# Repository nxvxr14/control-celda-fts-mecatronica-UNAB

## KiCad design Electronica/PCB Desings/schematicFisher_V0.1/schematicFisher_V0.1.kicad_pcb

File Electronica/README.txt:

*3D: Archivos .STL de componentes electrónicos no incluidos en las librerías de KiCad.
*Datasheets: Documentos en formato .pdf de las especificaciones de los distintos componentes utilizados en las tarjetas.
*Esquemáticos de referencia: Documentos .pdf con los esquemáticos de algunas tarjetas Arduino.
*Esquemáticos finales PDF: Documentos .pdf con los esquemáticos definitivos de las tarjetas del proyecto.
*Huellas y símbolos: Archivos de componentes necesarios que no se encuentran en las librerías nativas de KiCad.
*Imágenes: Archivos .PNG con las vistas 3D de las tarjetas.
*PCB Designs: Incluye los cuatro diseños electrónicos, con sus respectivos esquemáticos, símbolos, ruteados y referencias de componentes para su fabricación en JLCPCB, se abre con Kicad 7.0 o más:

-schematicFisher: Tarjeta para la adecuación de señales, convirtiendo voltajes de 9V a 24V y viceversa.
-schematicPLC: Tarjeta principal del PLC.
-schematicPowerSourcePLC: Tarjeta de alimentación para el PLC, con las fuentes de voltaje necesarias.
-schematicShieldPLC: Tarjeta diseñada para conectar un Arduino Mega al PLC.

*plcIMG.pretty: Archivo generado automáticamente por KiCad.
*Recortes de placa: No utilizado en el proyecto.
*Simulaciones: Simulaciones de los distintos circuitos implementados, realizadas en Proteus.

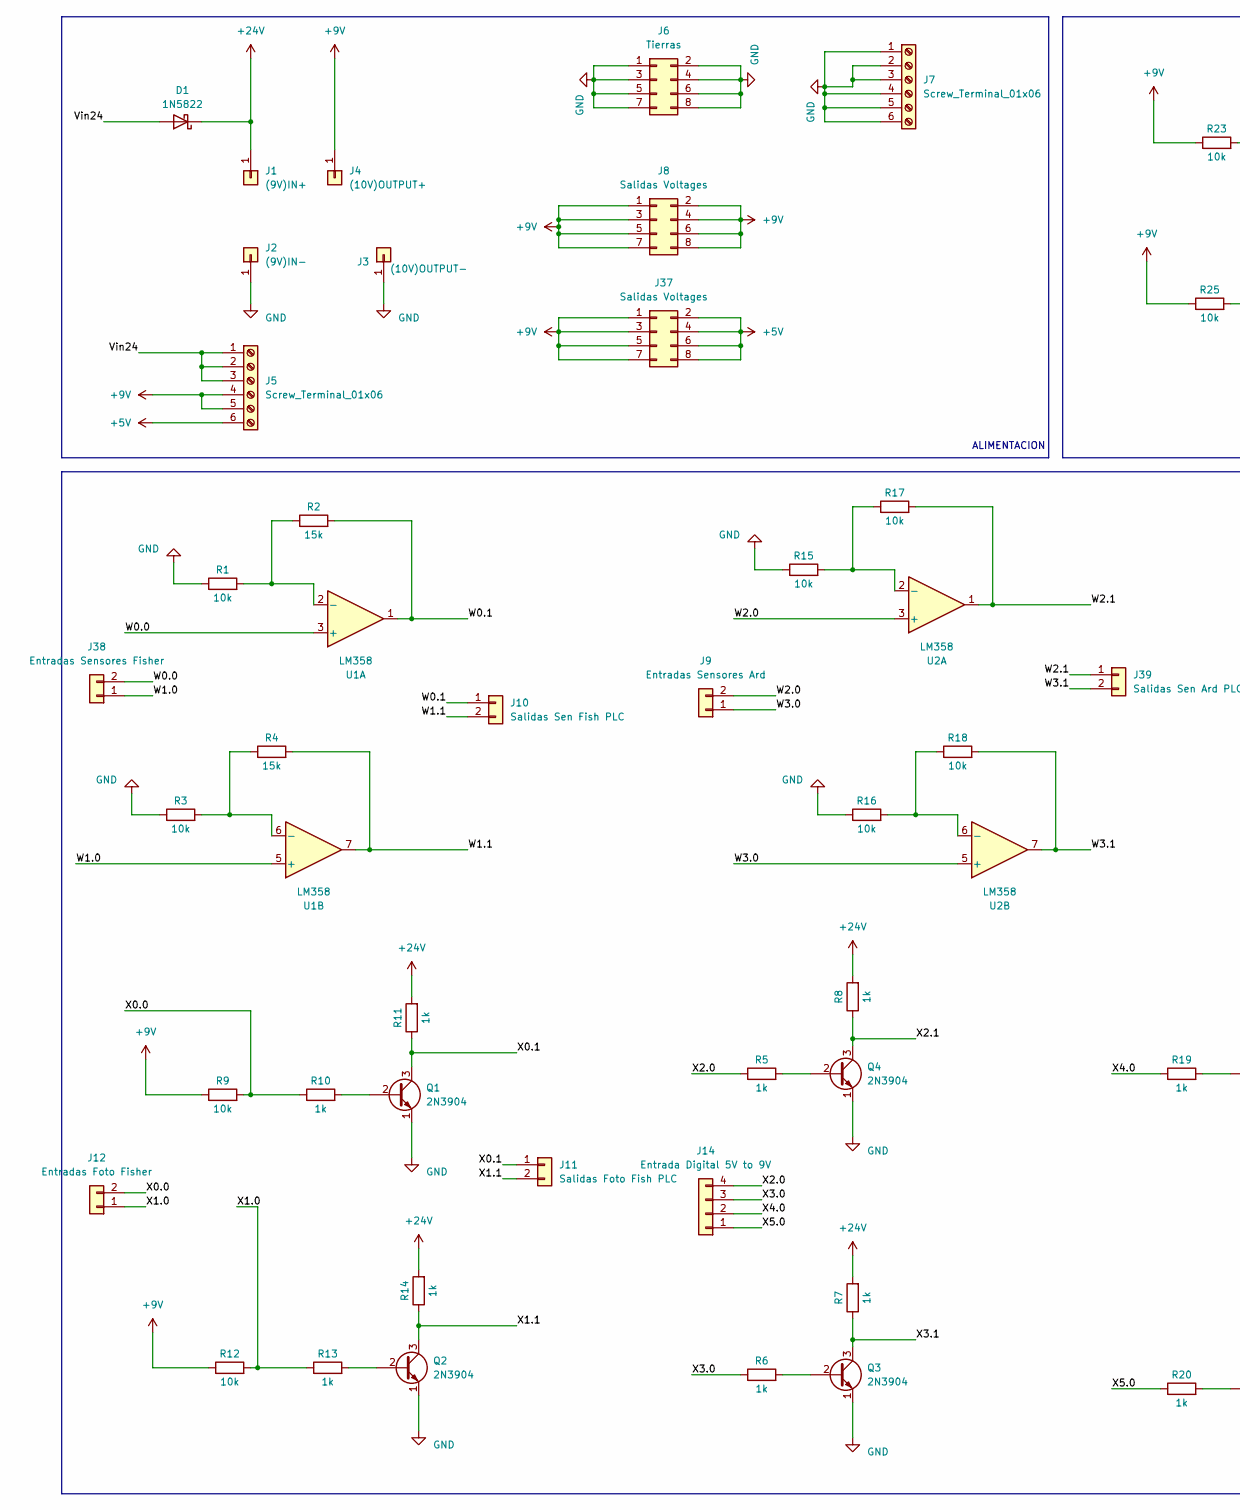
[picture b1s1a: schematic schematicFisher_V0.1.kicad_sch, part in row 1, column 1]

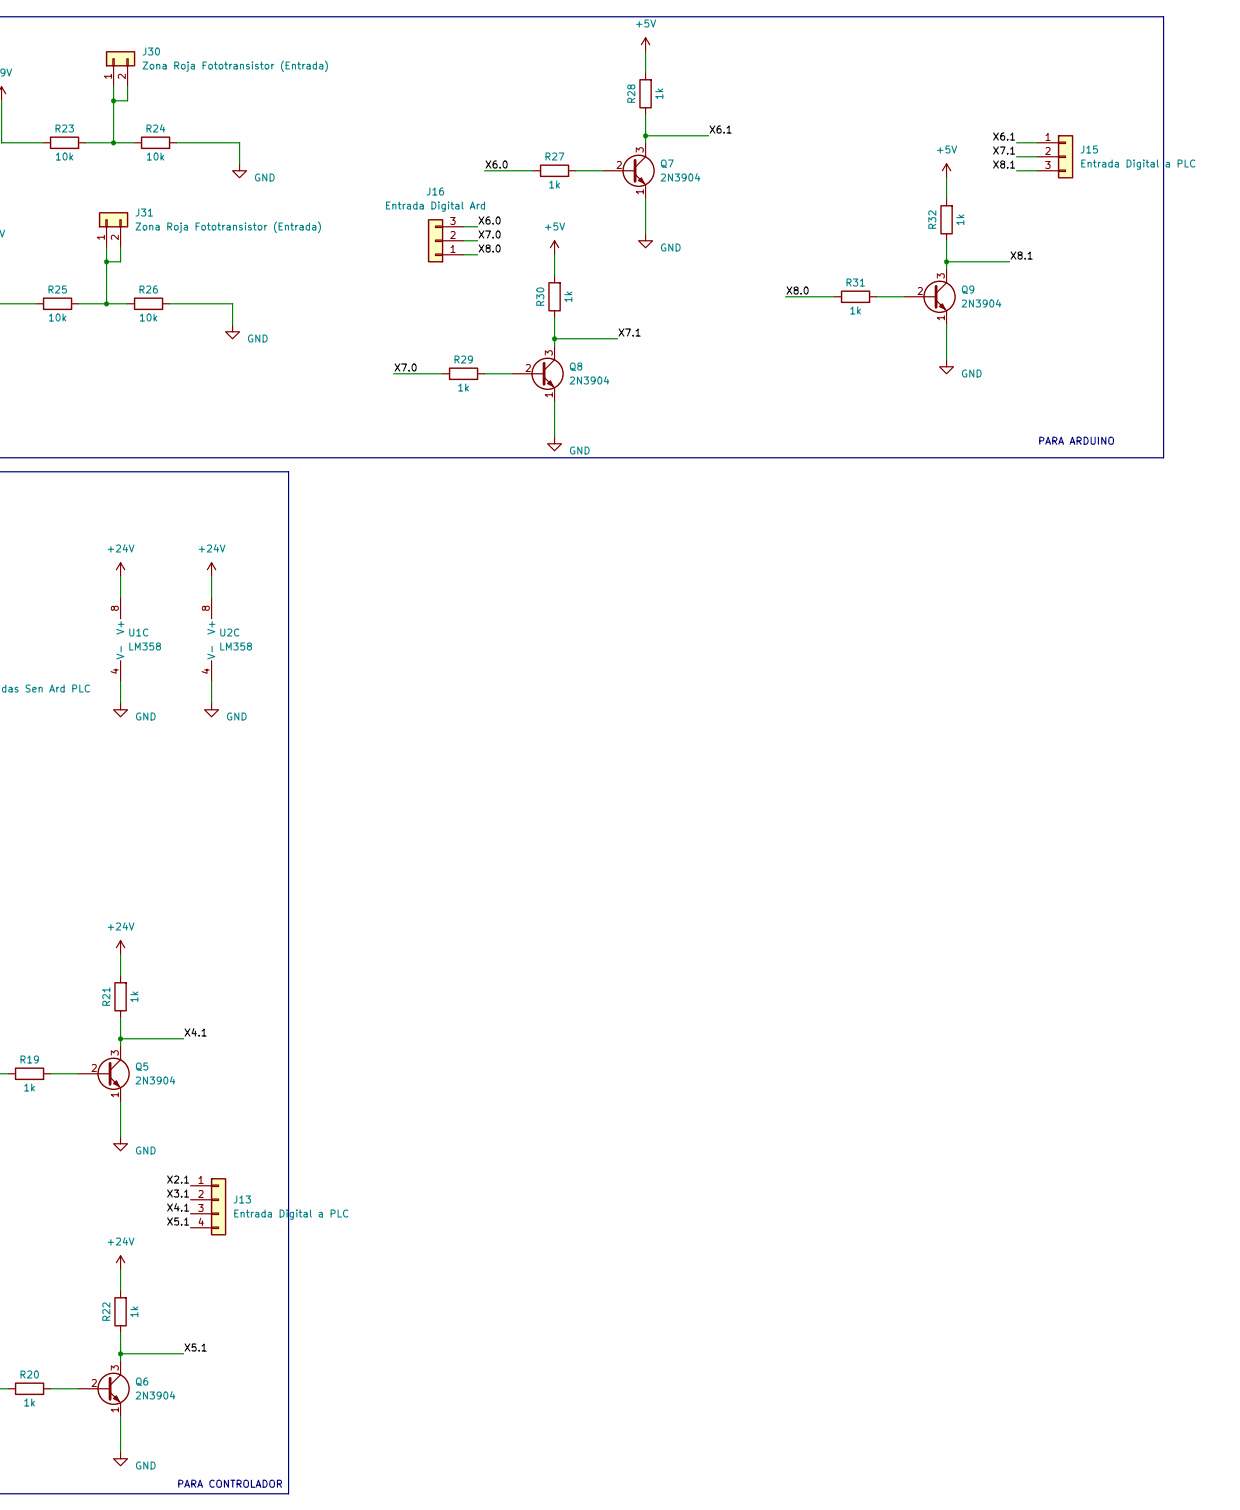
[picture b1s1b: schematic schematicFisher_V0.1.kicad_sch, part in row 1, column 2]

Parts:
D1: 1N5822; D_DO-201AD_P15.24mm_Horizontal
J1: (9V)IN+; PinSocket_1x01_P2.54mm_Vertical
J2: (9V)IN-; PinSocket_1x01_P2.54mm_Vertical
J3: (10V)OUTPUT-; PinSocket_1x01_P2.54mm_Vertical
J4: (10V)OUTPUT+; PinSocket_1x01_P2.54mm_Vertical
J5, J7: Screw_Terminal_01x06; TerminalBlock_Phoenix_MKDS-1,5-6_1x06_P5.00mm_Horizontal
J6: Tierras; PinHeader_2x04_P2.54mm_Vertical
J8, J37: Salidas Voltages; PinSocket_2x04_P2.54mm_Vertical
J9: Entradas Sensores Ard; PinHeader_1x02_P2.54mm_Vertical
J10: Salidas Sen Fish PLC; PinHeader_1x02_P2.54mm_Vertical
J11: Salidas Foto Fish PLC; PinHeader_1x02_P2.54mm_Vertical
J12: Entradas Foto Fisher; PinHeader_1x02_P2.54mm_Vertical
J13: Entrada Digital a PLC; PinHeader_1x04_P2.54mm_Vertical
J14: Entrada Digital 5V to 9V; PinHeader_1x04_P2.54mm_Vertical
J15: Entrada Digital a PLC; PinHeader_1x03_P2.54mm_Vertical
J16: Entrada Digital Ard; PinHeader_1x03_P2.54mm_Vertical
J30, J31: Zona Roja Fototransistor (Entrada); PinHeader_1x02_P2.54mm_Vertical
J38: Entradas Sensores Fisher; PinHeader_1x02_P2.54mm_Vertical
J39: Salidas Sen Ard PLC; PinHeader_1x02_P2.54mm_Vertical
Q1, Q2, Q3, Q4, Q5, Q6, Q7, Q8, Q9: 2N3904; TO-92_Inline
R1, R3, R9, R12, R15, R16, R17, R18, R23, R24, R25, R26: 10k; R_Axial_DIN0204_L3.6mm_D1.6mm_P5.08mm_Horizontal
R2, R4: 15k; R_Axial_DIN0204_L3.6mm_D1.6mm_P5.08mm_Horizontal
R5, R6, R7, R8, R10, R11, R13, R14, R19, R20, R21, R22, R27, R28, R29, R30, R31, R32: 1k; R_Axial_DIN0204_L3.6mm_D1.6mm_P5.08mm_Horizontal
U1, U2: LM358; DIP-8_W7.62mm_LongPads

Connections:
+5V: J5.6, J37.2, J37.4, J37.6, J37.8, R28.2, R30.2, R32.2
+9V: J4.1, J5.4, J5.5, J8.1, J8.2, J8.3, J8.4, J8.5, J8.6, J8.7, J8.8, J37.1, J37.3, J37.5, J37.7, R9.1, R12.1, R23.1, R25.1
+24V: D1.1 (K), J1.1, R7.2, R8.2, R11.2, R14.2, R21.2, R22.2, U1.8 (V+), U2.8 (V+)
/Vin24: D1.2 (A), J5.1, J5.2, J5.3
/W0.0: J38.2, U1.3 (+)
/W0.1: J10.1, R2.2, U1.1
/W1.0: J38.1, U1.5 (+)
/W1.1: J10.2, R4.2, U1.7
/W2.0: J9.2, U2.3 (+)
/W2.1: J39.1, R17.2, U2.1
/W3.0: J9.1, U2.5 (+)
/W3.1: J39.2, R18.2, U2.7
/X0.0: J12.2, R9.2, R10.1
/X0.1: J11.1, Q1.3 (C), R11.1
/X1.0: J12.1, R12.2, R13.1
/X1.1: J11.2, Q2.3 (C), R14.1
/X2.0: J14.4, R5.1
/X2.1: J13.1, Q4.3 (C), R8.1
/X3.0: J14.3, R6.1
/X3.1: J13.2, Q3.3 (C), R7.1
/X4.0: J14.2, R19.1
/X4.1: J13.3, Q5.3 (C), R21.1
/X5.0: J14.1, R20.1
/X5.1: J13.4, Q6.3 (C), R22.1
/X6.0: J16.3, R27.1
/X6.1: J15.1, Q7.3 (C), R28.1
/X7.0: J16.2, R29.1
/X7.1: J15.2, Q8.3 (C), R30.1
/X8.0: J16.1, R31.1
/X8.1: J15.3, Q9.3 (C), R32.1
GND: J2.1, J3.1, J6.1, J6.2, J6.3, J6.4, J6.5, J6.6, J6.7, J6.8, J7.1, J7.2, J7.3, J7.4, J7.5, J7.6, Q1.1 (E), Q2.1 (E), Q3.1 (E), Q4.1 (E), Q5.1 (E), Q6.1 (E), Q7.1 (E), Q8.1 (E), Q9.1 (E), R1.1, R3.1, R15.1, R16.1, R24.2, R26.2, U1.4 (V-), U2.4 (V-)
unnamed: J30.1, J30.2, R23.2, R24.1
unnamed: J31.1, J31.2, R25.2, R26.1
unnamed: Q1.2 (B), R10.2
unnamed: Q2.2 (B), R13.2
unnamed: Q3.2 (B), R6.2
unnamed: Q4.2 (B), R5.2
unnamed: Q5.2 (B), R19.2
unnamed: Q6.2 (B), R20.2
unnamed: Q7.2 (B), R27.2
unnamed: Q8.2 (B), R29.2
unnamed: Q9.2 (B), R31.2
unnamed: R1.2, R2.1, U1.2 (-)
unnamed: R3.2, R4.1, U1.6 (-)
unnamed: R15.2, R17.1, U2.2 (-)
unnamed: R16.2, R18.1, U2.6 (-)

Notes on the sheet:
PARA CONTROLADOR
PARA ARDUINO
ALIMENTACION

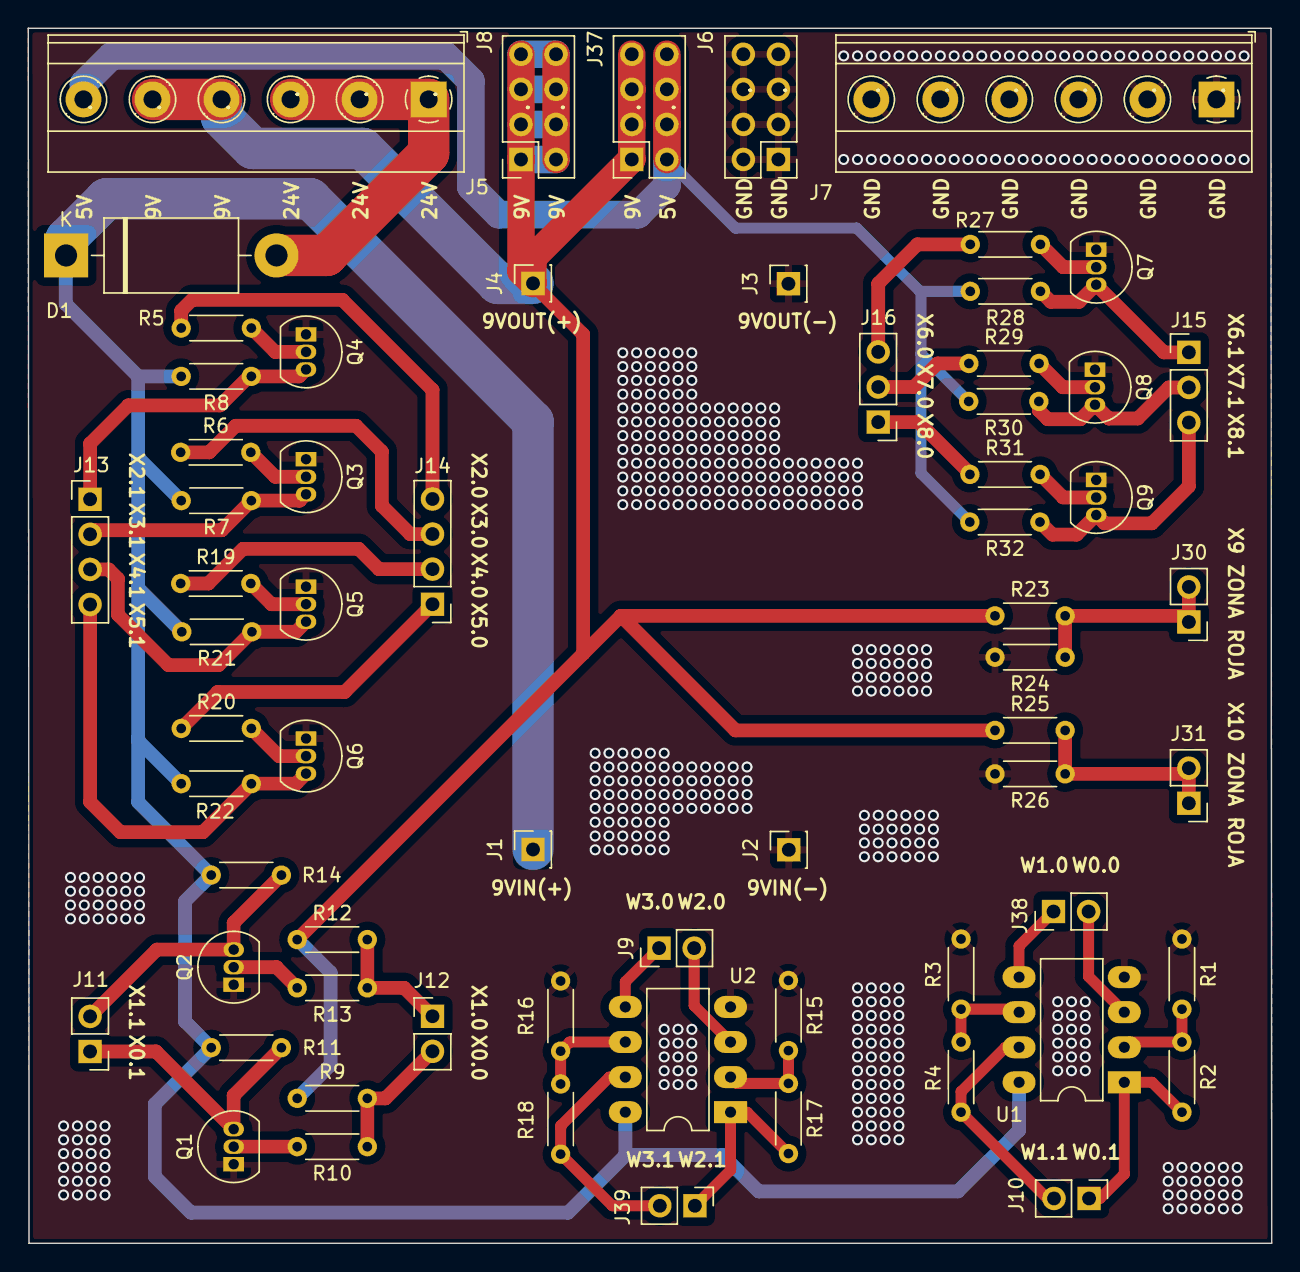
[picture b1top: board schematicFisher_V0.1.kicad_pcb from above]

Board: 2 copper layers, 90.1 x 88.0 mm, 65 parts (0 on the bottom side), 46 nets.

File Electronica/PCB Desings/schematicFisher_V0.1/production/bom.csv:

Designator,Footprint,Quantity,Value,LCSC Part #
D1,D_DO-201AD_P15.24mm_Horizontal,1,1N5822,
J1,PinSocket_1x01_P2.54mm_Vertical,1,(9V)IN+,
J10,PinHeader_1x02_P2.54mm_Vertical,1,Salidas Sen Fish PLC,
J11,PinHeader_1x02_P2.54mm_Vertical,1,Salidas Foto Fish PLC,
J12,PinHeader_1x02_P2.54mm_Vertical,1,Entradas Foto Fisher,
J13,PinHeader_1x04_P2.54mm_Vertical,1,Entrada Digital a PLC,
J14,PinHeader_1x04_P2.54mm_Vertical,1,Entrada Digital 5V to 9V,
J15,PinHeader_1x03_P2.54mm_Vertical,1,Entrada Digital a PLC,
J16,PinHeader_1x03_P2.54mm_Vertical,1,Entrada Digital Ard,
J2,PinSocket_1x01_P2.54mm_Vertical,1,(9V)IN-,
J3,PinSocket_1x01_P2.54mm_Vertical,1,(10V)OUTPUT-,
"J30, J31",PinHeader_1x02_P2.54mm_Vertical,2,Zona Roja Fototransistor (Entrada),
"J37, J8",PinSocket_2x04_P2.54mm_Vertical,2,Salidas Voltages,
J38,PinHeader_1x02_P2.54mm_Vertical,1,Entradas Sensores Fisher,
J39,PinHeader_1x02_P2.54mm_Vertical,1,Salidas Sen Ard PLC,
J4,PinSocket_1x01_P2.54mm_Vertical,1,(10V)OUTPUT+,
"J5, J7","TerminalBlock_Phoenix_MKDS-1,5-6_1x06_P5.00mm_Horizontal",2,Screw_Terminal_01x06,
J6,PinHeader_2x04_P2.54mm_Vertical,1,Tierras,
J9,PinHeader_1x02_P2.54mm_Vertical,1,Entradas Sensores Ard,
"Q1, Q2, Q3, Q4, Q5, Q6, Q7, Q8, Q9",TO-92_Inline,9,2N3904,
"R1, R12, R15, R16, R17, R18, R23, R24, R25, R26, R3, R9",R_Axial_DIN0204_L3.6mm_D1.6mm_P5.08mm_Horizontal,12,10k,
"R10, R11, R13, R14, R19, R20, R21, R22, R27, R28, R29, R30, R31, R32, R5, R6, R7, R8",R_Axial_DIN0204_L3.6mm_D1.6mm_P5.08mm_Horizontal,18,1k,
"R2, R4",R_Axial_DIN0204_L3.6mm_D1.6mm_P5.08mm_Horizontal,2,15k,
"U1, U2",DIP-8_W7.62mm_LongPads,2,LM358,

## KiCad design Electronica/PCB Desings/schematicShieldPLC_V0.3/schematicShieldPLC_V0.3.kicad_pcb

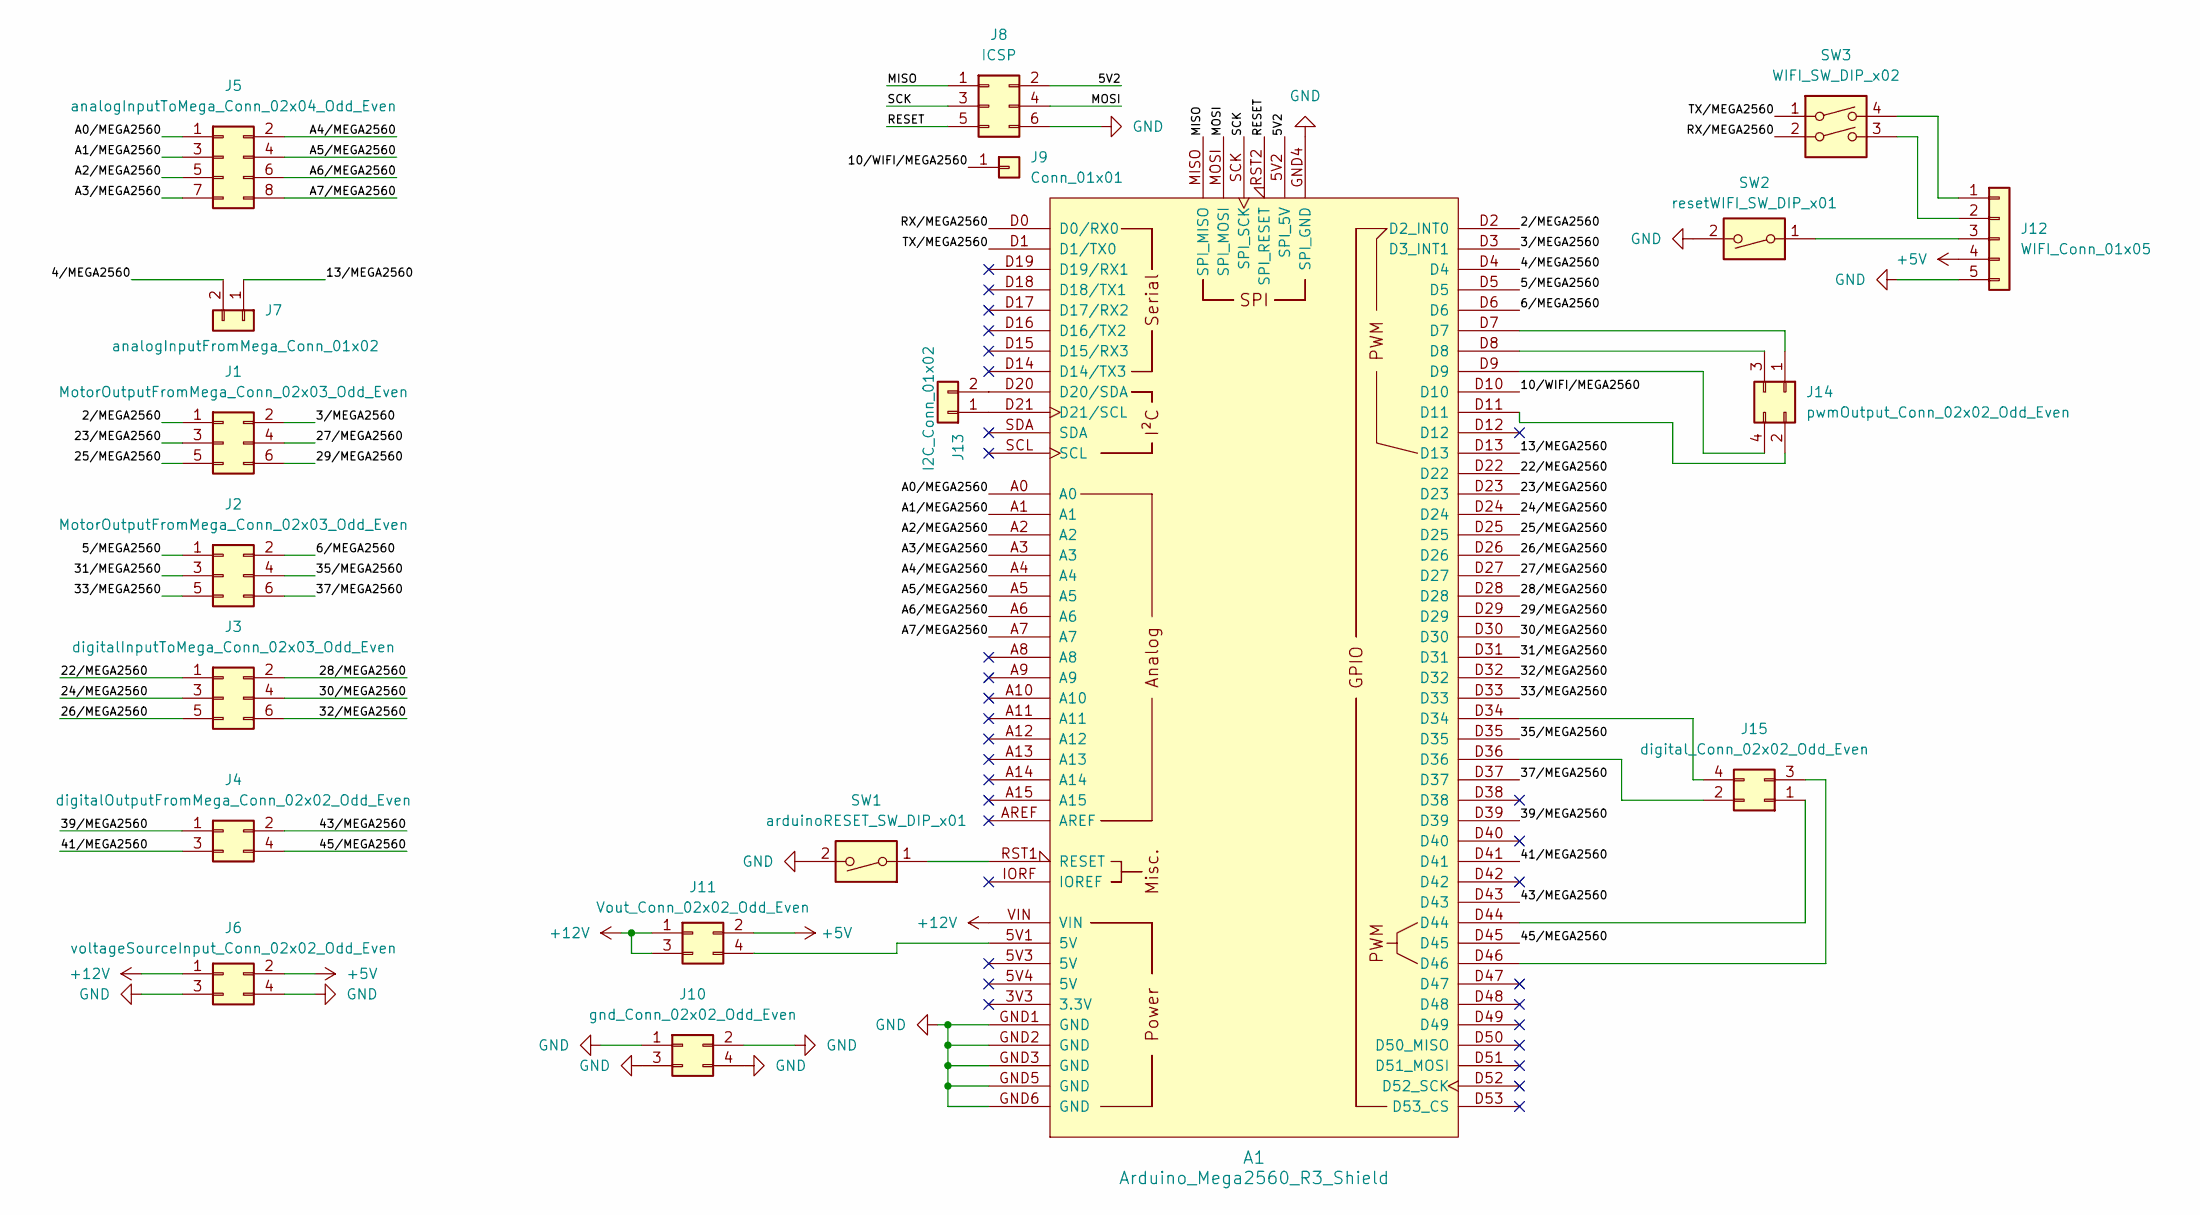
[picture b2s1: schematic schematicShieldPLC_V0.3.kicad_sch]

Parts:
A1: Arduino_Mega2560_R3_Shield
J1, J2: MotorOutputFromMega_Conn_02x03_Odd_Even; PinSocket_2x03_P2.54mm_Vertical
J3: digitalInputToMega_Conn_02x03_Odd_Even; PinSocket_2x03_P2.54mm_Vertical
J4: digitalOutputFromMega_Conn_02x02_Odd_Even; PinSocket_2x02_P2.54mm_Vertical
J5: analogInputToMega_Conn_02x04_Odd_Even; PinSocket_2x04_P2.54mm_Vertical
J6: voltageSourceInput_Conn_02x02_Odd_Even; PinSocket_2x02_P2.54mm_Vertical
J7: analogInputFromMega_Conn_01x02; PinSocket_1x02_P2.54mm_Vertical
J8: ICSP; PinSocket_2x03_P2.54mm_Vertical
J9: Conn_01x01; PinSocket_1x01_P2.54mm_Vertical
J10: gnd_Conn_02x02_Odd_Even; PinSocket_2x02_P2.54mm_Vertical
J11: Vout_Conn_02x02_Odd_Even; PinSocket_2x02_P2.54mm_Vertical
J12: WIFI_Conn_01x05; PinSocket_1x05_P2.54mm_Vertical
J13: I2C_Conn_01x02; PinSocket_1x02_P2.54mm_Horizontal
J14: pwmOutput_Conn_02x02_Odd_Even; PinSocket_2x02_P2.54mm_Vertical
J15: digital_Conn_02x02_Odd_Even; PinSocket_2x02_P2.54mm_Horizontal
SW1: arduinoRESET_SW_DIP_x01; SW_DIP_SPSTx01_Slide_9.78x4.72mm_W7.62mm_P2.54mm
SW2: resetWIFI_SW_DIP_x01; SW_DIP_SPSTx01_Slide_9.78x4.72mm_W7.62mm_P2.54mm
SW3: WIFI_SW_DIP_x02; SW_DIP_SPSTx02_Slide_9.78x7.26mm_W7.62mm_P2.54mm

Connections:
+5V: J6.2, J11.2, J12.4
+12V: A1.VIN, J6.1, J11.1, J11.3
/2/MEGA2560: A1.D2 (D2_INT0), J1.1
/3/MEGA2560: A1.D3 (D3_INT1), J1.2
/4/MEGA2560: A1.D4, J7.2
/5V2: A1.5V2 (SPI_5V), J8.2
/5/MEGA2560: A1.D5, J2.1
/6/MEGA2560: A1.D6, J2.2
/10/WIFI/MEGA2560: A1.D10, J9.1
/13/MEGA2560: A1.D13, J7.1
/22/MEGA2560: A1.D22, J3.1
/23/MEGA2560: A1.D23, J1.3
/24/MEGA2560: A1.D24, J3.3
/25/MEGA2560: A1.D25, J1.5
/26/MEGA2560: A1.D26, J3.5
/27/MEGA2560: A1.D27, J1.4
/28/MEGA2560: A1.D28, J3.2
/29/MEGA2560: A1.D29, J1.6
/30/MEGA2560: A1.D30, J3.4
/31/MEGA2560: A1.D31, J2.3
/32/MEGA2560: A1.D32, J3.6
/33/MEGA2560: A1.D33, J2.5
/35/MEGA2560: A1.D35, J2.4
/37/MEGA2560: A1.D37, J2.6
/39/MEGA2560: A1.D39, J4.1
/41/MEGA2560: A1.D41, J4.3
/43/MEGA2560: A1.D43, J4.2
/45/MEGA2560: A1.D45, J4.4
/A0/MEGA2560: A1.A0, J5.1
/A1/MEGA2560: A1.A1, J5.3
/A2/MEGA2560: A1.A2, J5.5
/A3/MEGA2560: A1.A3, J5.7
/A4/MEGA2560: A1.A4, J5.2
/A5/MEGA2560: A1.A5, J5.4
/A6/MEGA2560: A1.A6, J5.6
/A7/MEGA2560: A1.A7, J5.8
/MISO: A1.MISO (SPI_MISO), J8.1
/MOSI: A1.MOSI (SPI_MOSI), J8.4
/RESET: A1.RST2 (SPI_RESET), J8.5
/RX/MEGA2560: A1.D0 (D0/RX0), SW3.2
/SCK: A1.SCK (SPI_SCK), J8.3
/TX/MEGA2560: A1.D1 (D1/TX0), SW3.1
GND: A1.GND1 (GND), A1.GND2 (GND), A1.GND3 (GND), A1.GND4 (SPI_GND), A1.GND5 (GND), A1.GND6 (GND), J6.3, J6.4, J8.6, J10.1, J10.2, J10.3, J10.4, J12.5, SW1.2, SW2.2
unnamed: A1.D20 (D20/SDA), J13.2
unnamed: A1.D21 (D21/SCL), J13.1
unnamed: A1.RST1 (RESET), SW1.1
unnamed: A1.5V1 (5V), J11.4
unnamed: J12.1, SW3.4
unnamed: J12.2, SW3.3
unnamed: J12.3, SW2.1
unnamed: A1.D7, J14.1
unnamed: A1.D11, J14.2
unnamed: A1.D8, J14.3
unnamed: A1.D9, J14.4
unnamed: A1.D44, J15.1
unnamed: A1.D36, J15.2
unnamed: A1.D46, J15.3
unnamed: A1.D34, J15.4

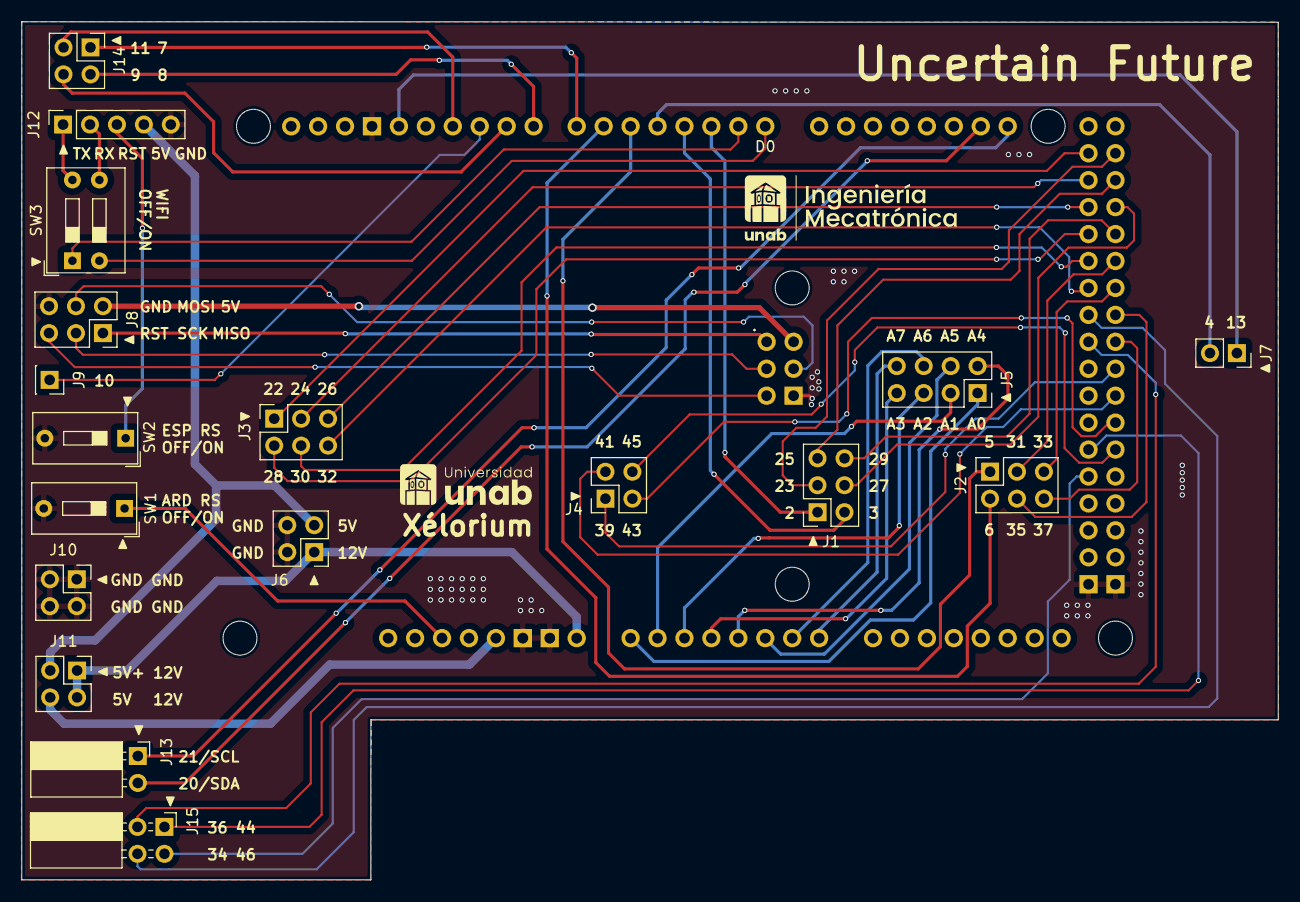
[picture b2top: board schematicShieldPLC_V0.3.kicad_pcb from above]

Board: 2 copper layers, 118.5 x 80.9 mm, 19 parts (0 on the bottom side), 58 nets.

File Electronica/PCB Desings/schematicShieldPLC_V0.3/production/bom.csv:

Designator,Footprint,Quantity,Value,LCSC Part #
A1,Arduino_Mega2560_R3_Shield,1,Arduino_Mega2560_R3_Shield,
"J1, J2",PinSocket_2x03_P2.54mm_Vertical,2,MotorOutputFromMega_Conn_02x03_Odd_Even,
J10,PinSocket_2x02_P2.54mm_Vertical,1,gnd_Conn_02x02_Odd_Even,
J11,PinSocket_2x02_P2.54mm_Vertical,1,Vout_Conn_02x02_Odd_Even,
J12,PinSocket_1x05_P2.54mm_Vertical,1,WIFI_Conn_01x05,
J13,PinSocket_1x02_P2.54mm_Horizontal,1,I2C_Conn_01x02,
J14,PinSocket_2x02_P2.54mm_Vertical,1,pwmOutput_Conn_02x02_Odd_Even,
J15,PinSocket_2x02_P2.54mm_Horizontal,1,digital_Conn_02x02_Odd_Even,
J3,PinSocket_2x03_P2.54mm_Vertical,1,digitalInputToMega_Conn_02x03_Odd_Even,
J4,PinSocket_2x02_P2.54mm_Vertical,1,digitalOutputFromMega_Conn_02x02_Odd_Even,
J5,PinSocket_2x04_P2.54mm_Vertical,1,analogInputToMega_Conn_02x04_Odd_Even,
J6,PinSocket_2x02_P2.54mm_Vertical,1,voltageSourceInput_Conn_02x02_Odd_Even,
J7,PinSocket_1x02_P2.54mm_Vertical,1,analogInputFromMega_Conn_01x02,
J8,PinSocket_2x03_P2.54mm_Vertical,1,ICSP,
J9,PinSocket_1x01_P2.54mm_Vertical,1,Conn_01x01,
SW1,SW_DIP_SPSTx01_Slide_9.78x4.72mm_W7.62mm_P2.54mm,1,arduinoRESET_SW_DIP_x01,
SW2,SW_DIP_SPSTx01_Slide_9.78x4.72mm_W7.62mm_P2.54mm,1,resetWIFI_SW_DIP_x01,
SW3,SW_DIP_SPSTx02_Slide_9.78x7.26mm_W7.62mm_P2.54mm,1,WIFI_SW_DIP_x02,
